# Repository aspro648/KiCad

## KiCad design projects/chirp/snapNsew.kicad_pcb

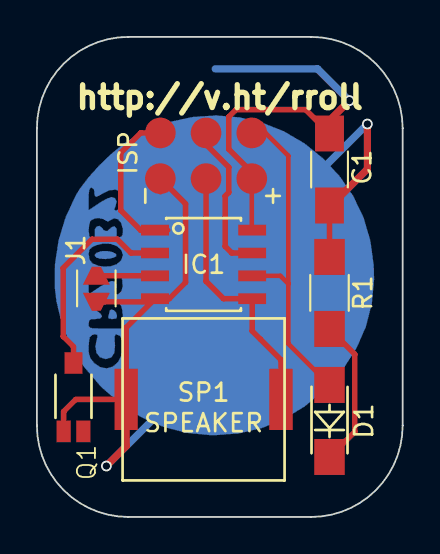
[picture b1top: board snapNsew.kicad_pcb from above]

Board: 2 copper layers, 20.3 x 26.7 mm, 9 parts (1 on the bottom side), 9 nets.

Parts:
BT1: Battery; BATT_CR2032_SMD
C1: 0.1 uF; C_1206_HandSoldering
CON1: ISP; Pin_Header_Straight_2x03_Pitch2.54mm
D1: LED; LED_1206_HandSoldering
IC1: ATTINY85; SOIC-8_3.9x4.9mm_Pitch1.27mm
J1: JMP; R_1206_HandSoldering
Q1: LIGHT; PHOTO_TRANS
R1: 330; R_1206_HandSoldering
SP1: SPEAKER; PS1240_piezo

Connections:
+BATT: BT1.1, C1.2, CON1.2, IC1.8
GND: BT1.2, C1.1, CON1.6, IC1.4, J1.1, Q1.1, R1.1, SP1.1
unnamed: CON1.1, D1.2, IC1.6
unnamed: CON1.3, IC1.7
unnamed: CON1.4, IC1.5, SP1.2
unnamed: CON1.5, IC1.1
unnamed: D1.1, R1.2
unnamed: IC1.2, Q1.3
unnamed: IC1.3, J1.2

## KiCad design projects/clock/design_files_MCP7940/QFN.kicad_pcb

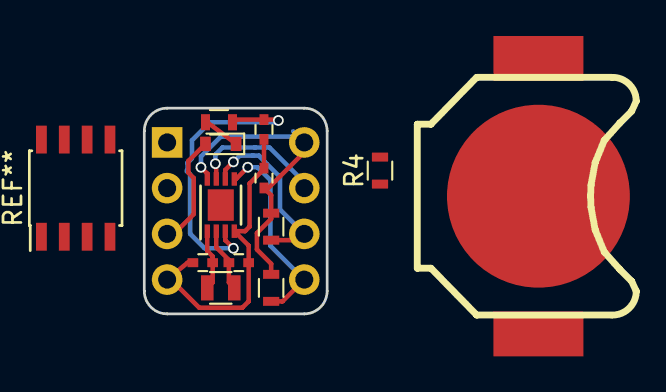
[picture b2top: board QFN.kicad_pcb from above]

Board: 2 copper layers, 10.2 x 11.4 mm, 14 parts (0 on the bottom side), 10 nets.

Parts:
BAT***: 12mm; BATT_12mm
C1: 0.1uF; C_0402
C2: 100pF; C_0402
CX1, CX2: 10pF; C_0402
Crystal1: 32.768; R_0805
D1: D_Schottky; D_0603
JL1: Conn_01x04; Pin_Header_Straight_1x04_Pitch2.54mm
JR1: Conn_01x04; Pin_Header_Straight_1x04_Pitch2.54mm
R1: 1K; R_0603
R2, R3: 2K; R_0603
R4: 10K; R_0603
U1: RTC; DFN-8-1EP_3x2mm_Pitch0.5mm

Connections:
/MFP: JR1.2, R4.1, U1.7
/SCL: JR1.3, R2.1, U1.6
/SDA: JR1.4, R3.1, U1.5
/VBAT: D1.2, JL1.3
GND: C1.1, C2.1, CX1.2, CX2.2, JL1.4, U1.4
unnamed: C2.2, R1.2, U1.3
unnamed: CX1.1, Crystal1.1, U1.1
unnamed: CX2.1, Crystal1.2, U1.2
unnamed: D1.1, R1.1
VCC: C1.2, JR1.1, R2.2, R3.2, R4.2, U1.8

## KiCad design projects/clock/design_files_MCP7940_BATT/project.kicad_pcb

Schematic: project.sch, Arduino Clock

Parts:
BT1: Battery_Cell; BATT_12mm_TH
P1, P2, P3, P4: Pin; Pin_Header_Straight_1x01_Pitch2.54mm

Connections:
/VBAT: BT1.1 (+), P1.1
GND: BT1.2 (-), P2.1, P3.1, P4.1

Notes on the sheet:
https://www.electronicshub.org/arduino-4-digit-7-segment-led-display/
https://www.digikey.com/product-detail/en/adafruit-industries-llc/811/1528-1509-ND/5774235

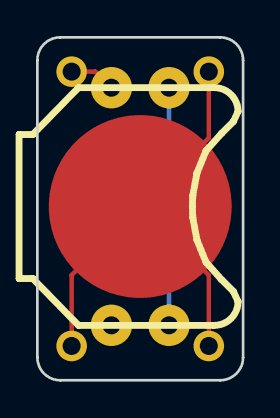
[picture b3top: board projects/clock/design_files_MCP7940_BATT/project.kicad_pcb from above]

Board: 2 copper layers, 11.4 x 19.1 mm, 5 parts (0 on the bottom side), 2 nets.

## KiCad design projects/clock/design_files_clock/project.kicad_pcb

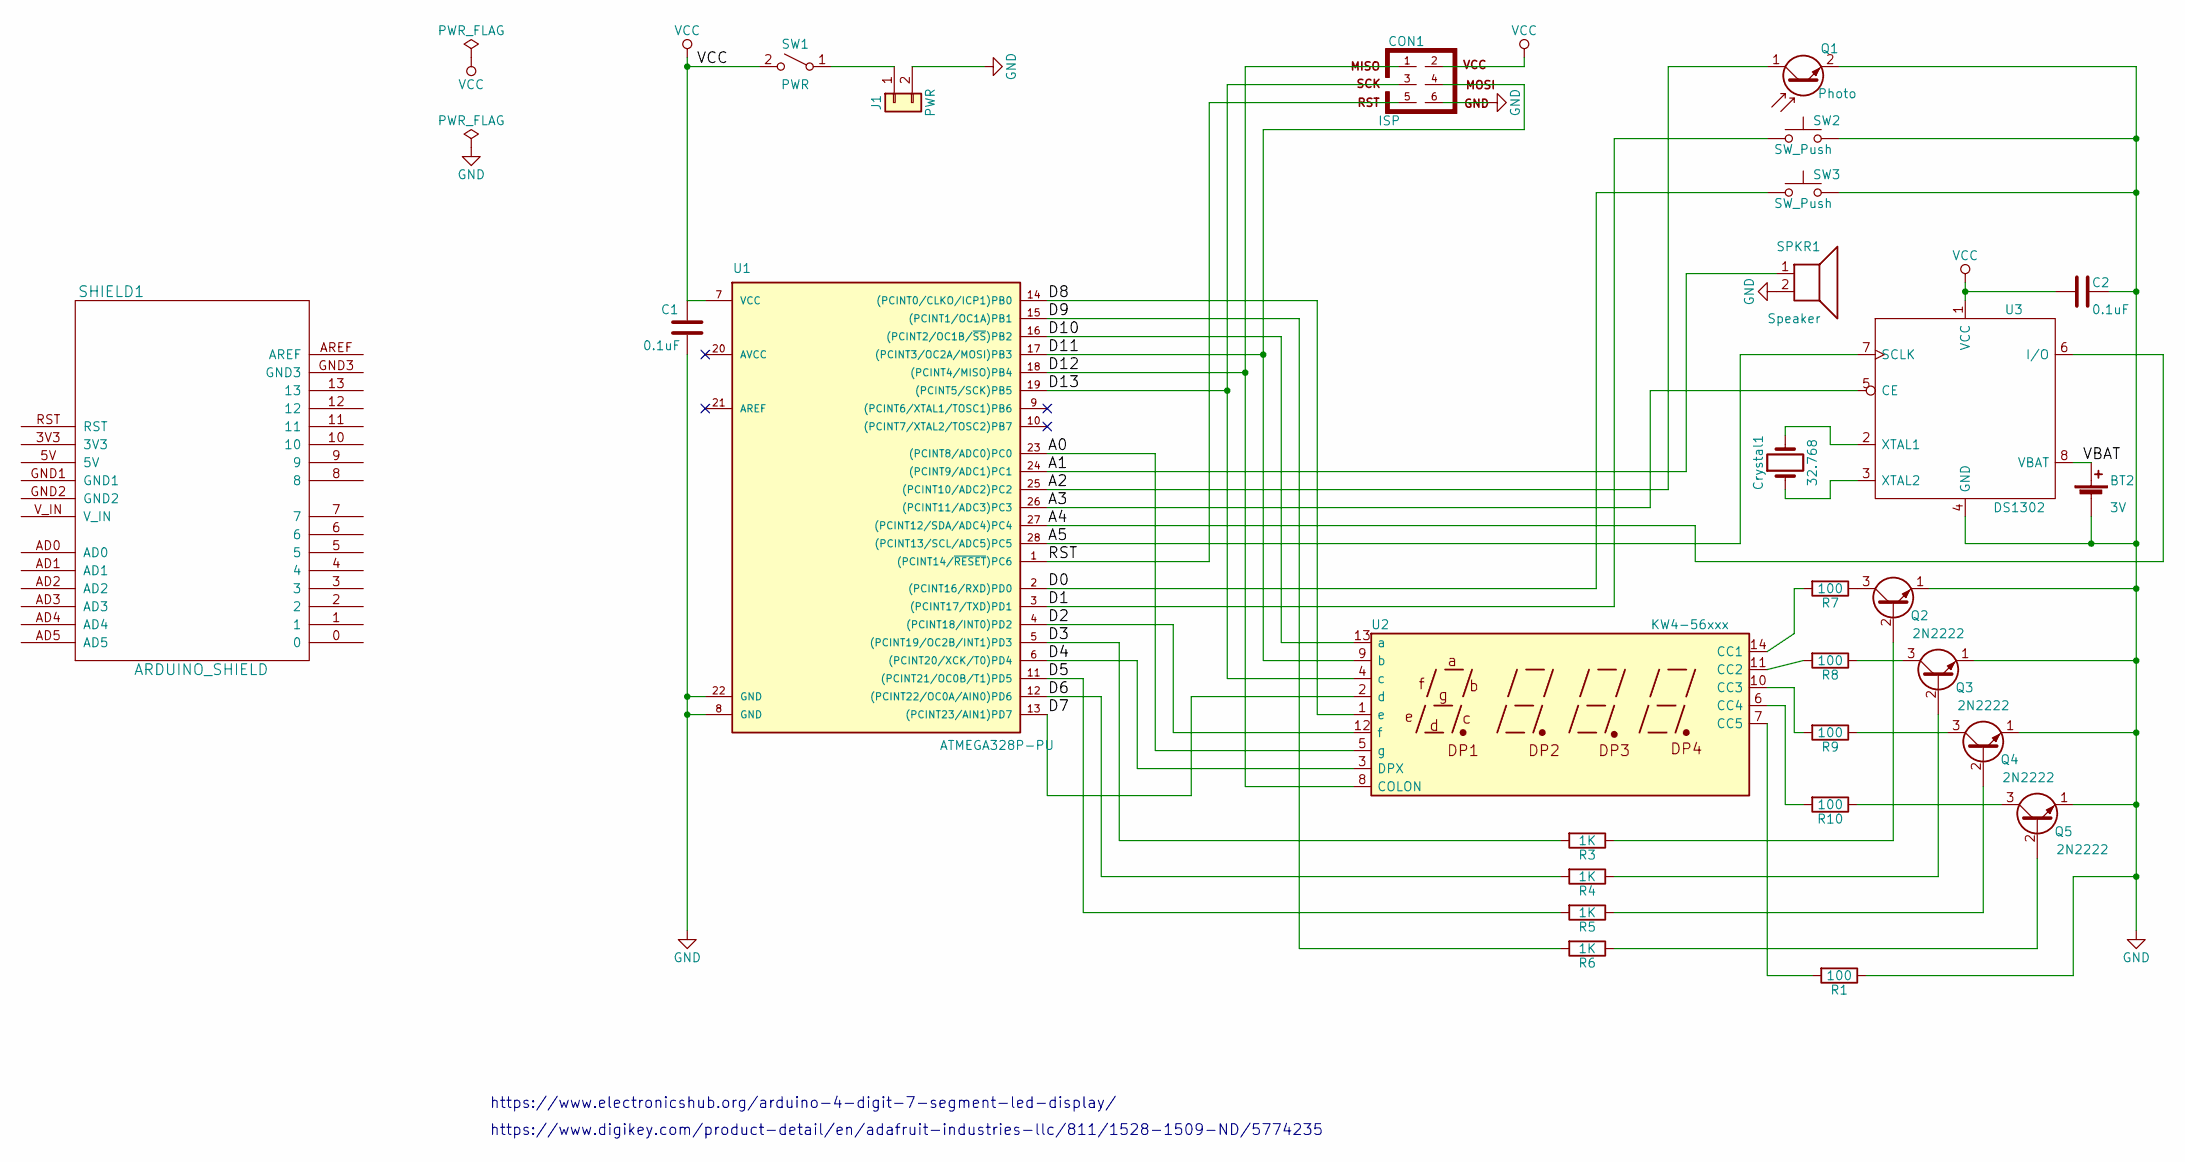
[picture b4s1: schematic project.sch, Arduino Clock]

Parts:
BT2: 3V; BATT_12mm_TH
C1, C2: 0.1uF; C_Disc_D3.4mm_W2.1mm_P2.50mm
CON1: ISP; AVR-ISP-6
Crystal1: 32.768; Crystal_C38-LF_d3.0mm_l8.0mm_Horizontal_1EP_style1
J1: PWR; PhoenixContact_MC-G_02x3.50mm_Angled
Q1: Photo; PHOTO_TRANS
Q2, Q3, Q4, Q5: 2N2222; TO-92_NPN_EBC_wide
R1, R7, R8, R9, R10: 100; Resistor_Horz
R3, R4, R5, R6: 1K; Resistor_Horz
SHIELD1: ARDUINO_SHIELD
SPKR1: Speaker; PS1240_piezo
SW1: PWR; SW_Micro_SPST
SW2, SW3: SW_Push; SW_PUSH_SMALL
U1: ATMEGA328P-PU; DIP-28_W7.62mm
U2: KW4-56xxx; CA56-12CGKWA
U3: DS1302; DIP-8_W7.62mm

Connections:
/A0: U1.23 ((PCINT8/ADC0)PC0), U2.5 (g)
/A1: SPKR1.1, U1.24 ((PCINT9/ADC1)PC1)
/A2: Q1.1 (C), U1.25 ((PCINT10/ADC2)PC2)
/A3: U1.26 ((PCINT11/ADC3)PC3), U3.5 (CE)
/A4: U1.27 ((PCINT12/SDA/ADC4)PC4), U3.6 (I/O)
/A5: U1.28 ((PCINT13/SCL/ADC5)PC5), U3.7 (SCLK)
/D0: SW3.1, U1.2 ((PCINT16/RXD)PD0)
/D1: SW2.1, U1.3 ((PCINT17/TXD)PD1)
/D2: U1.4 ((PCINT18/INT0)PD2), U2.12 (f)
/D3: R3.2, U1.5 ((PCINT19/OC2B/INT1)PD3)
/D4: U1.6 ((PCINT20/XCK/T0)PD4), U2.3 (DPX)
/D5: R5.2, U1.11 ((PCINT21/OC0B/T1)PD5)
/D6: R4.2, U1.12 ((PCINT22/OC0A/AIN0)PD6)
/D7: U1.13 ((PCINT23/AIN1)PD7), U2.2 (d)
/D8: U1.14 ((PCINT0/CLKO/ICP1)PB0), U2.1 (e)
/D9: R6.2, U1.15 ((PCINT1/OC1A)PB1)
/D10: U1.16 ((PCINT2/OC1B/~SS~)PB2), U2.13 (a)
/D11: CON1.4, U1.17 ((PCINT3/OC2A/MOSI)PB3), U2.9 (b)
/D12: CON1.1, U1.18 ((PCINT4/MISO)PB4), U2.8 (COLON)
/D13: CON1.3, U1.19 ((PCINT5/SCK)PB5), U2.4 (c)
/RST: CON1.5, U1.1 ((PCINT14/~RESET~)PC6)
/VBAT: BT2.1 (+), U3.8 (VBAT)
GND: BT2.2 (-), C1.2, C2.1, CON1.6, J1.2, Q1.2 (E), Q2.1 (E), Q3.1 (E), Q4.1 (E), Q5.1 (E), R1.1, SPKR1.2, SW2.2, SW3.2, U1.8 (GND), U1.22 (GND), U3.4 (GND)
unnamed: Crystal1.1, U3.3 (XTAL2)
unnamed: Crystal1.2, U3.2 (XTAL1)
unnamed: J1.1, SW1.1 (A)
unnamed: Q2.2 (B), R3.1
unnamed: Q2.3 (C), R7.1
unnamed: Q3.2 (B), R4.1
unnamed: Q3.3 (C), R8.1
unnamed: Q4.2 (B), R5.1
unnamed: Q4.3 (C), R9.1
unnamed: Q5.2 (B), R6.1
unnamed: Q5.3 (C), R10.1
unnamed: R1.2, U2.7 (CC5)
unnamed: R7.2, U2.14 (CC1)
unnamed: R8.2, U2.11 (CC2)
unnamed: R9.2, U2.10 (CC3)
unnamed: R10.2, U2.6 (CC4)
VCC: C1.1, C2.2, CON1.2, SW1.2 (B), U1.7 (VCC), U3.1 (VCC)

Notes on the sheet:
https://www.electronicshub.org/arduino-4-digit-7-segment-led-display/
https://www.digikey.com/product-detail/en/adafruit-industries-llc/811/1528-1509-ND/5774235

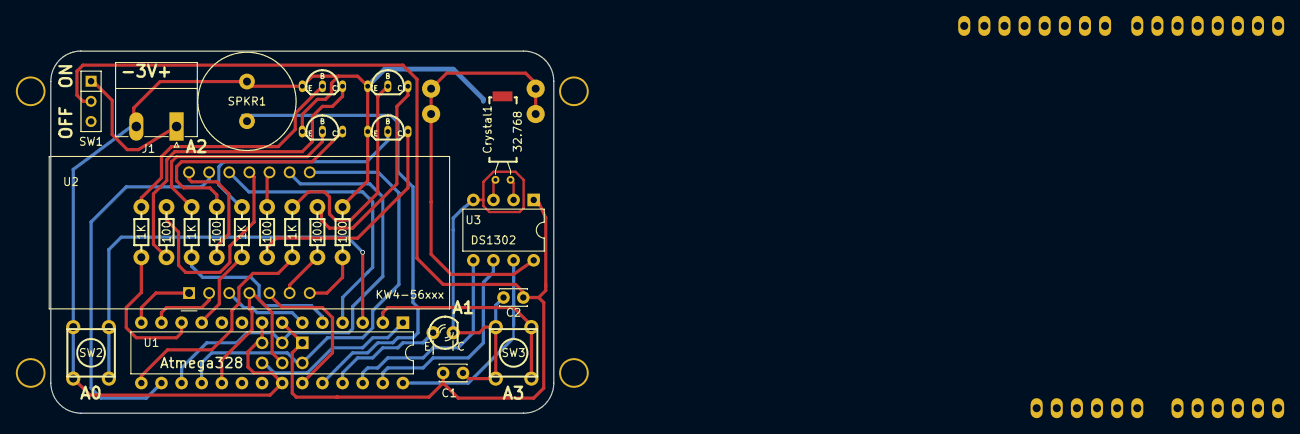
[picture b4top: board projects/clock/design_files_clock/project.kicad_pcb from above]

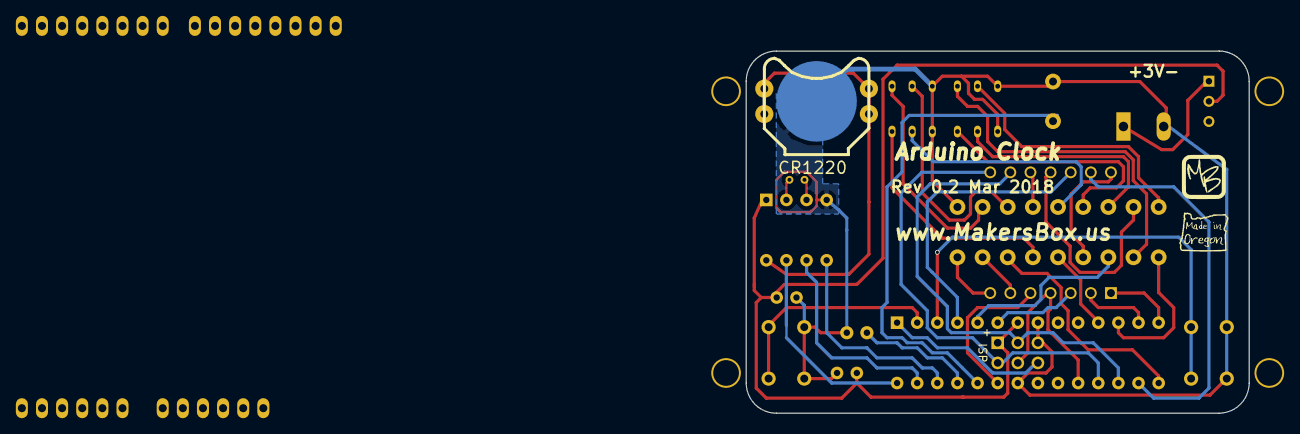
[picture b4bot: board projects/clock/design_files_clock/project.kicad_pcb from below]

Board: 2 copper layers, 63.5 x 45.7 mm, 34 parts (2 on the bottom side), 40 nets.

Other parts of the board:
H1, H1#2, H1#3, H1#4: Hole; Pin_Header_Straight_1x01_Pitch2.54mm
VAL: MB225rev
VAL#2: MadeInOregonRev25

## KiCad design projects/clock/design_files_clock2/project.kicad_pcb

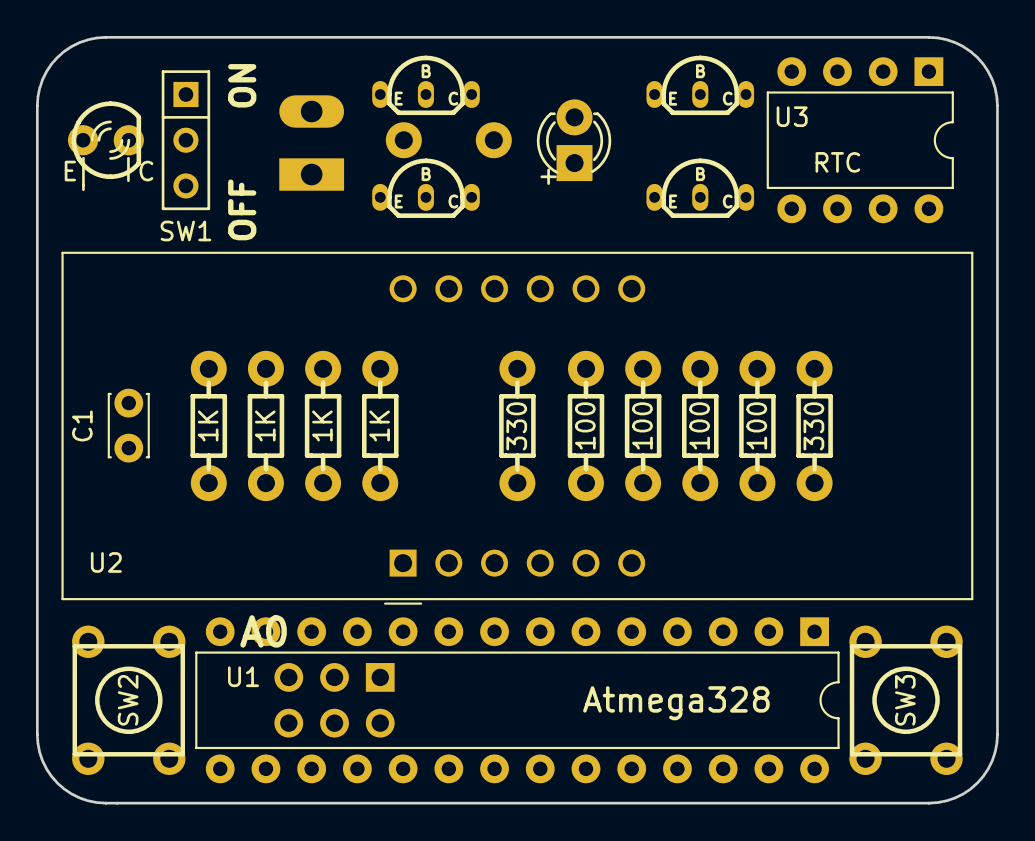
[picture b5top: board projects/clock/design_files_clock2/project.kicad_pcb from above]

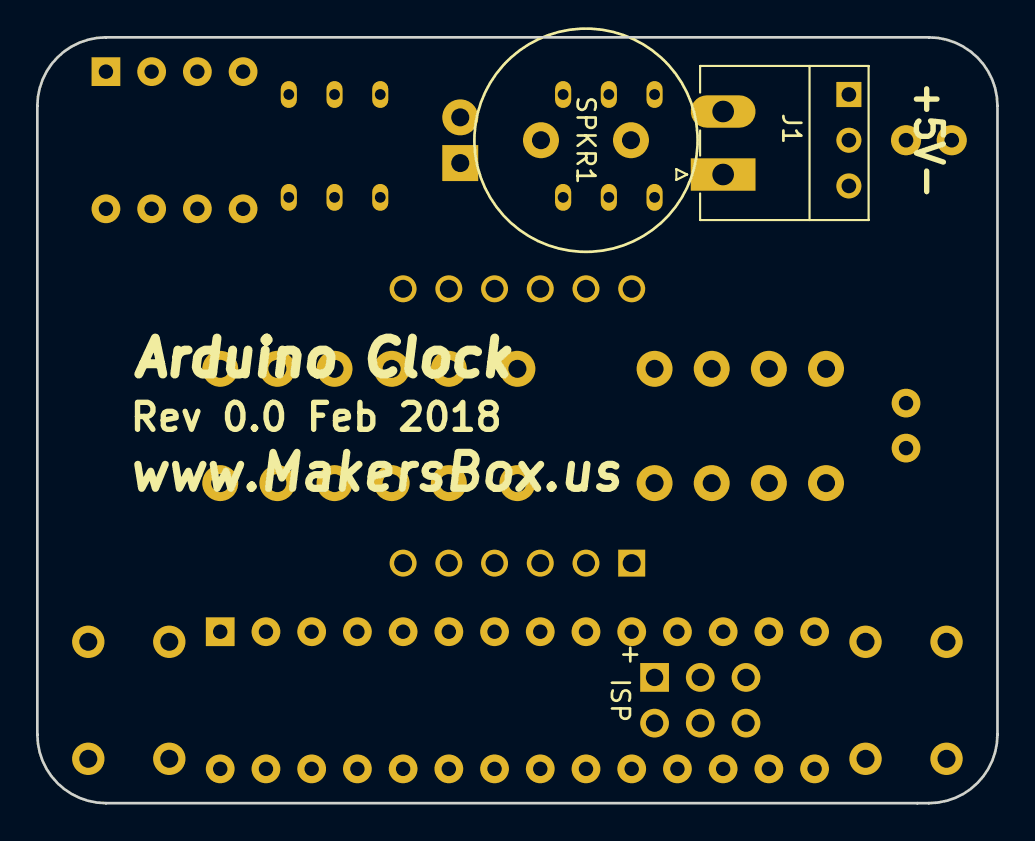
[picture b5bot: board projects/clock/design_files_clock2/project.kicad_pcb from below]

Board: 2 copper layers, 53.3 x 42.5 mm, 26 parts (3 on the bottom side), 37 nets, no tracks yet.

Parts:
C1: 0.1uF; C_Disc_D3.4mm_W2.1mm_P2.50mm
CON1: ISP; AVR-ISP-6
D2: LED; LED-3MM
J1: PWR; PhoenixContact_MC-G_02x3.50mm_Angled
Q1: Photo; PHOTO_TRANS
Q2, Q3, Q4, Q5: 2N2222; TO-92_NPN_EBC_wide
R1, R2: 330; Resistor_Horz
R3, R4, R5, R6: 1K; Resistor_Horz
R7, R8, R9, R10: 100; Resistor_Horz
SPKR1: Speaker; PS1240_piezo
SW1: PWR; SW_Micro_SPST
SW2, SW3: SW_Push; SW_PUSH_SMALL
U1: ATMEGA328P-PU; DIP-28_W7.62mm
U2: CC56-12CGKWA; CA56-12CGKWA
U3: RTC; DIP-8_W7.62mm

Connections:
/A0: Q1.1, U1.23
/A1: SW2.1, U1.24
/A2: SW3.1, U1.25
/A3: SPKR1.1, U1.26
/A4: U1.27, U3.5
/A5: U1.28, U3.6
/D0: R1.2, U1.2
/D1: R2.2, U1.3
/D2: U1.4, U2.11
/D3: U1.5, U2.7
/D4: U1.6, U2.4
/D5: U1.11, U2.2
/D6: U1.12, U2.1
/D7: U1.13, U2.10
/D8: U1.14, U2.5
/D9: U1.15, U2.3
/D10: R3.2, U1.16
/D11: CON1.4, R4.2, U1.17
/D12: CON1.1, R5.2, U1.18
/D13: CON1.3, R6.2, U1.19
GND: C1.2, CON1.6, D2.1, J1.2, Q1.2, Q2.1, Q3.1, Q4.1, Q5.1, SPKR1.2, SW2.2, SW3.2, U1.8, U1.22, U3.4
unnamed: CON1.5, U1.1
unnamed: D2.2, R2.1
unnamed: J1.1, SW1.1
unnamed: Q2.2, R3.1
unnamed: Q2.3, R7.1
unnamed: Q3.2, R4.1
unnamed: Q3.3, R8.1
unnamed: Q4.2, R5.1
unnamed: Q4.3, R9.1
unnamed: Q5.2, R6.1
unnamed: Q5.3, R10.1
unnamed: R7.2, U2.12
unnamed: R8.2, U2.9
unnamed: R9.2, U2.8
unnamed: R10.2, U2.6
VCC: C1.1, CON1.2, SW1.2, U1.7, U3.8
